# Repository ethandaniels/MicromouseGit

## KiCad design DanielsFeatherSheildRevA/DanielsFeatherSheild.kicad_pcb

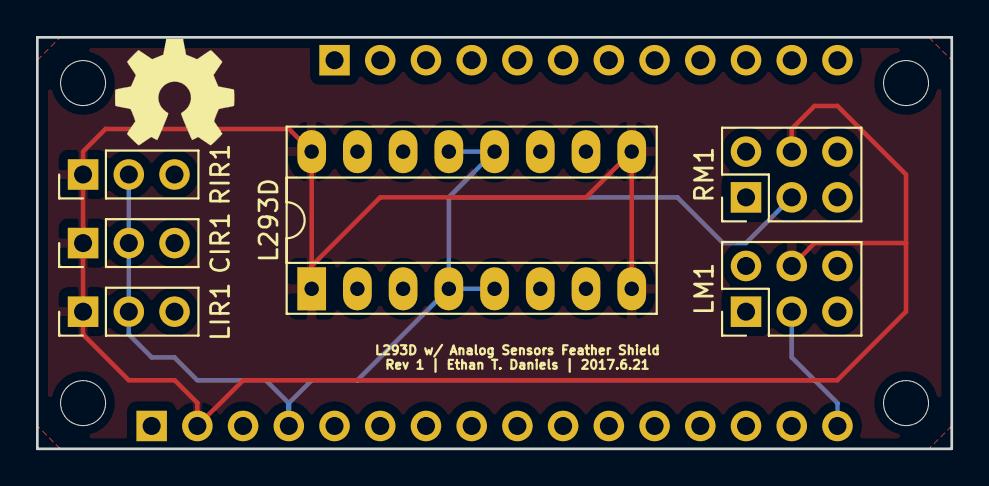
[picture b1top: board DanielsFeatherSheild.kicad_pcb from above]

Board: 4 copper layers, 50.8 x 22.9 mm, 6 parts (0 on the bottom side), 6 nets.

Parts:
CIR1: CONN_01X03; Socket_Strip_Straight_1x03_Pitch2.54mm
L293D: L293D; DIP-16_W7.62mm_Socket_LongPads
LIR1: CONN_01X03; Socket_Strip_Straight_1x03_Pitch2.54mm
LM1: CONN_02X03; Pin_Header_Straight_2x03_Pitch2.54mm
RIR1: CONN_01X03; Socket_Strip_Straight_1x03_Pitch2.54mm
RM1: CONN_02X03; Pin_Header_Straight_2x03_Pitch2.54mm

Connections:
+3V3: CIR1.1, L293D.1, L293D.8, L293D.9, L293D.16, LIR1.1, LM1.4, RIR1.1, RM1.4
GND: CIR1.2, L293D.4, L293D.5, L293D.12, L293D.13, LIR1.2, LM1.3, RIR1.2, RM1.3
LM+: L293D.3, LM1.2
LM-: L293D.6, LM1.1
RM+: L293D.14, RM1.2
RM-: L293D.11, RM1.1

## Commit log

2017-09-20 FirstCommit
